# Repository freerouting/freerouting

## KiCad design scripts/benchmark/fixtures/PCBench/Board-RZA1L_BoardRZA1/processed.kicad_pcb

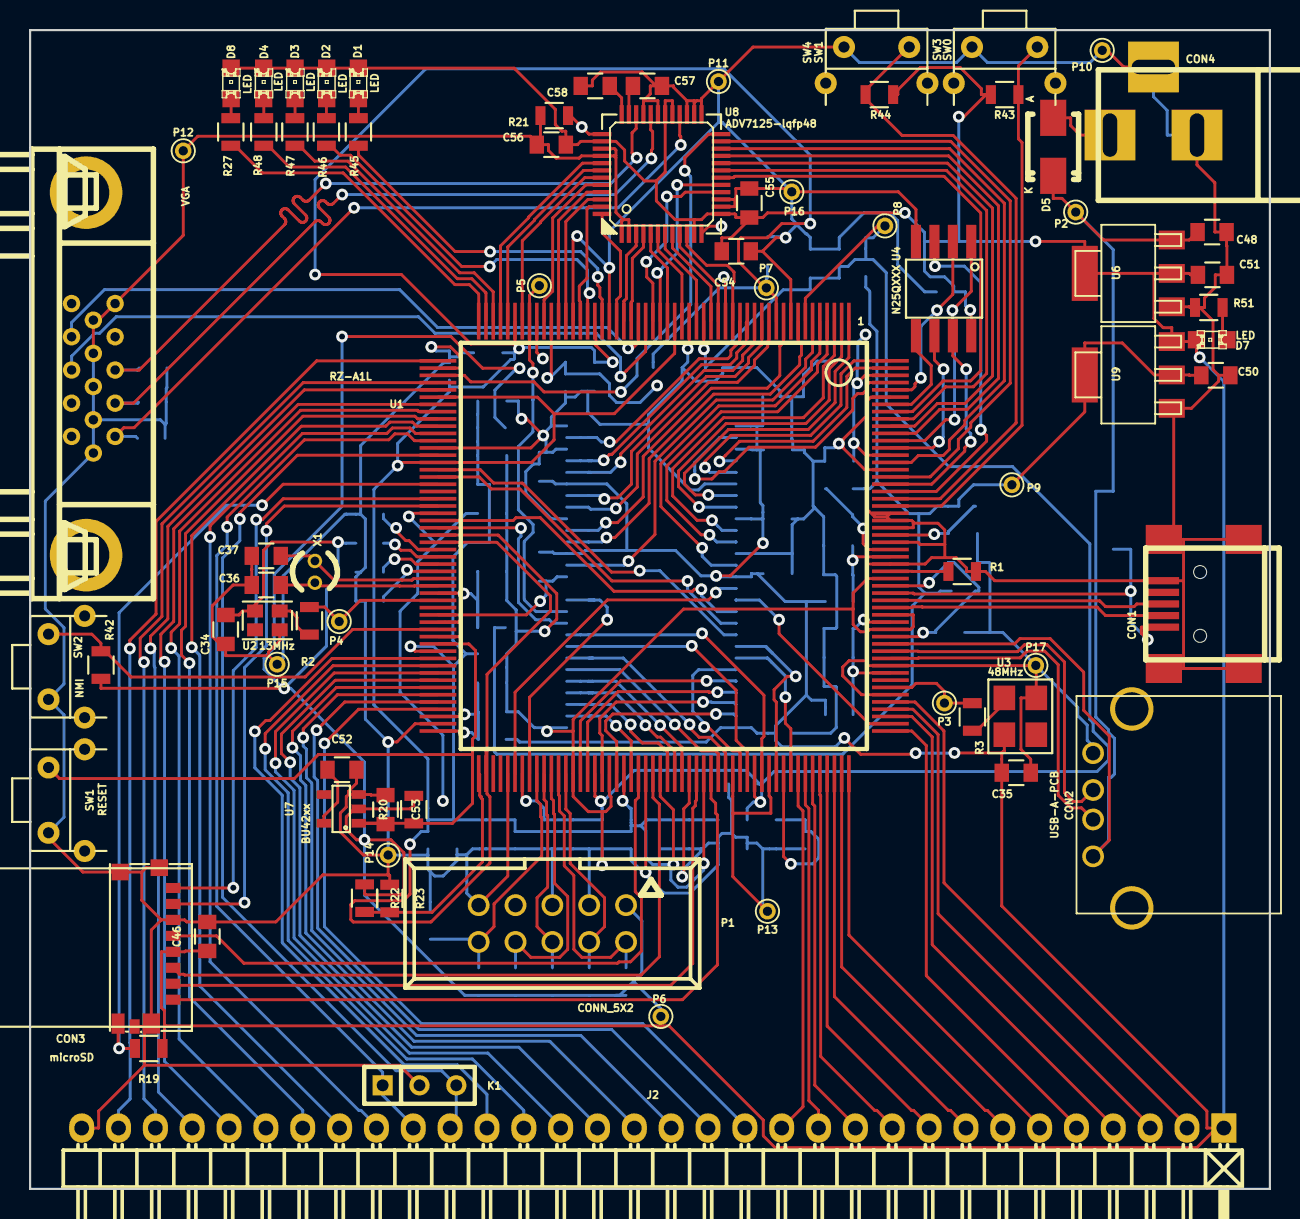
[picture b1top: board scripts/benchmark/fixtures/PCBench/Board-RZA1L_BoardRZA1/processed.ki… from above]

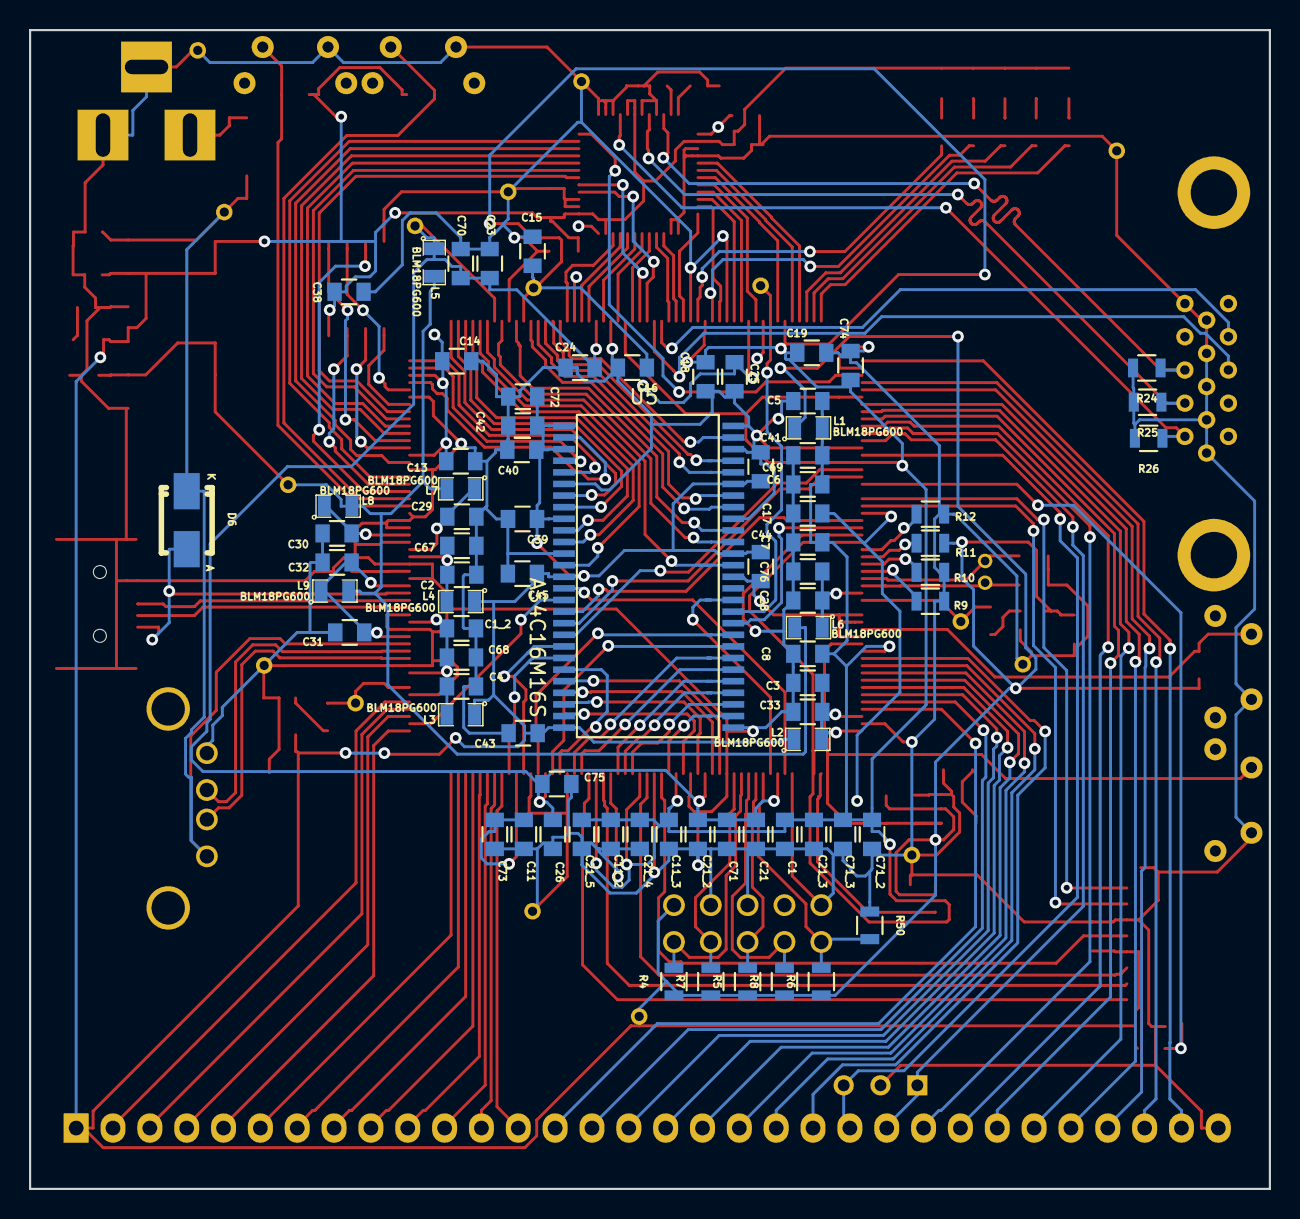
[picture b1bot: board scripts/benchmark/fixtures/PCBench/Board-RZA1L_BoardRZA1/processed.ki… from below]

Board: 4 copper layers, 85.5 x 79.9 mm, 154 parts (78 on the bottom side), 167 nets.

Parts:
C1, C1_2, C2, C3, C4, C5, C6, C7, C8, C11, C11_2, C11_3, C13, C14, C15, C16, C17, C18, C19, C21, C21_2, C21_3, C21_4, C21_5, C23, C24, C25, C26, C28, C29, C30, C31, C32, C33, C34, C35, C38, C39, C40, C41, C42, C43, C44, C45, C51, C52, C54, C55, C56, C57, C58: 100n; C_0805
C36, C37: 10p; C_0805
C46, C50, C53: 1u; C_0805
C48, C67, C68, C69, C70, C71_3: 10u; C_0805
C71, C71_2, C72, C73, C74, C75, C76: 100p; C_0805
CON1: USB-MINI-B; USB_MINI_B
CON2: USB-A-PCB; USB_A
CON3: microSD
CON4: BARREL_JACK
D1, D2, D3, D4, D7, D8: LED; LED-0805
D5, D6: MBRA210; Diode-SMA_Standard
J1: VGA; DB_15F-VGA
J2: SUPP32; Pin_Header_Angled_1x32
K1: CONN_3; SIL-3
L1, L2, L3, L4, L5, L6, L7, L8, L9: BLM18PG600; SM0805
P1: CONN_5X2; VASCH5x2
P2, P3, P4, P5, P6, P7, P8, P9, P10, P11, P12, P13, P14, P15, P16, P17: CONN_1; PINTST
R1: 5K6; R_0805
R2, R3, R51: 220R; R_0805
R4, R5, R6, R7, R8, R9, R10, R11, R12, R19, R20, R22, R23, R42, R43, R44, R50: 10k; R_0805
R21: 560R; R_0805
R24, R25, R26: 75R; R_0805
R27, R45, R46, R47, R48: 1k; R_0805
SW1: RESET; RigthAnglePush
SW2: NMI; RigthAnglePush
SW3: SW0; RigthAnglePush
SW4: SW1; RigthAnglePush
U1: RZ-A1L; PQFP208
U2: 13MHz; OSC_2x2p5
U3: 48MHz; OSC_4PIN
U4: N25QXXX; SOP2-8
U5: AS4C16M16S; TSOP_II_54
U6: NCP1117ST33T3G; sot223
U7: BU42xx; SSOP-5
U8: ADV7125-lqfp48; lqfp48
U9: NCP1117ST12T3G; sot223
X1: 32.768k; Crystal_Round_Vertical_3mm

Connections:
+1.2V: C50.1, L5.2, L6.2, L7.2, L8.2, L9.2, P9.1, U9.2
+3.3V: C34.1, C35.1, C38.1, C39.1, C40.1, C41.1, C42.1, C43.1, C44.1, C45.1, C46.1, C51.1, C54.2, C55.2, C56.2, C72.1, CON3.4, D1.2, D2.2, D3.2, D4.2, D7.2, D8.2, J2.1, L1.1, L2.1, L3.1, L4.1, P1.1, P6.1, R4.1, R5.1, R6.1, R7.1, R8.1, R11.1, R19.1, R20.2, R22.1, R42.2, R43.2, R44.2, U2.4, U3.4, U4.8, U5.1, U5.3, U5.9, U5.14, U5.27, U5.43, U5.49, U6.2, U7.2, U8.11, U8.13, U8.29, U8.30, U8.38, U9.3
/+5v: C48.1, CON2.1, D5.2, D6.2, P2.1, U1.169, U6.3
/AVcc: C3.1, C33.2, L2.2, U1.102, U1.104
/DCIN: CON4.1, D5.1
/DM_CLK: R10.2, U1.81
/D_D+: CON1.3, U1.175
/D_D-: CON1.2, U1.174
/H_D+: CON2.3, U1.168
/H_D-: CON2.2, U1.167
/JTAG_TCK: P1.4, R7.2, U1.117
/JTAG_TDI: P1.8, R8.2, U1.115
/JTAG_TDO: P1.6, R5.2, U1.114
/JTAG_TMS: P1.2, R4.2, U1.116
/JTAG_TRST: P1.10, R6.2, R50.2, U1.113
/LCD_DATA0: U1.192, U8.23
/LCD_DATA1: U1.194, U8.22
/LCD_DATA2: U1.198, U8.21
/LCD_DATA3: U1.199, U8.20
/LCD_DATA4: U1.200, U8.19
/LCD_DATA5: U1.201, U8.18
/LCD_DATA6: U1.27, U8.17
/LCD_DATA7: U1.28, U8.16
/LCD_DATA8: U1.17, U8.10
/LCD_DATA9: U1.19, U8.9
/LCD_DATA10: U1.20, U8.8
/LCD_DATA11: U1.22, U8.7
/LCD_DATA12: U1.24, U8.6
/LCD_DATA13: U1.26, U8.5
/LCD_DATA14: U1.31, U8.4
/LCD_DATA15: U1.32, U8.3
/LCD_DATA16: U1.33, U8.48
/LCD_DATA17: U1.38, U8.47
/LCD_DATA18: U1.40, U8.46
/LCD_DATA19: U1.41, U8.45
/LCD_DATA20: U1.43, U8.44
/LCD_DATA21: U1.46, U8.43
/LCD_DATA22: U1.48, U8.42
/LCD_DATA23: U1.49, U8.41
/LCD_HSYNC: J1.13, U1.29
/LCD_PCLK: U1.55, U8.24
/LCD_VSYNC: J1.14, U1.30
/LED0: R45.1, U1.35
/LED1: R46.1, U1.37
/LED2: R47.1, U1.50
/LED3: R48.1, U1.51
/LED4: R27.1, U1.52
/MD_BOOT0: R12.2, U1.79
/MD_BOOT1: R11.2, U1.80
/MD_CLKS: R9.2, U1.82
/NMI: R42.1, SW2.1, U1.90
/P1_0: J2.13, U1.149
/P1_1: J2.12, U1.150
/P1_2: J2.11, U1.151
/P1_3: J2.10, U1.152
/P1_4: J2.9, U1.153
/P1_5: J2.8, U1.154
/P1_6: J2.7, U1.155
/P1_7: J2.6, U1.156
/P1_8: J2.21, U1.94
/P1_9: J2.20, U1.95
/P1_10: J2.19, U1.96
/P1_11: J2.18, U1.97
/P1_12: J2.17, U1.98
/P1_13: J2.16, U1.99
/P1_14: J2.15, U1.100
/P1_15: J2.14, U1.101
/P2_7: J2.4, U1.159
/P2_8: J2.3, U1.160
/P2_9: J2.2, U1.161
/P3_15: J2.5, U1.157
/P7_3: J2.31, U1.53
/P7_5: J2.30, U1.56
/P7_6: J2.29, U1.57
/P7_7: J2.28, U1.59
/P7_8: J2.27, U1.60
/P7_9: J2.26, U1.61
/P7_10: J2.25, U1.62
/P7_11: J2.24, U1.63
/P8_12(RXD): J2.23, K1.1, U1.64
/P8_13(TXD): J2.22, K1.3, U1.66
/PLLVCC: C28.1, C76.1, L6.1, U1.85
/PVCC: C1.1, C5.1, C6.1, C7.1, C8.1, C11.1, C11_2.1, C11_3.1, C13.1, C14.1, C15.1, C16.1, C18.1, C19.1, C21_3.1, C21_4.1, C21_5.1, C69.1, C71_2.1, C71_3.1, C73.1, C74.1, L1.2, P7.1, U1.11, U1.25, U1.36, U1.47, U1.58, U1.67, U1.78, U1.93, U1.106, U1.125, U1.130, U1.136, U1.147, U1.195, U1.206
/RAM_A1: U1.119, U5.23
/RAM_A2: U1.120, U5.24
/RAM_A3: U1.122, U5.25
/RAM_A4: U1.124, U5.26
/RAM_A5: U1.126, U5.29
/RAM_A6: U1.131, U5.30
/RAM_A7: U1.132, U5.31
/RAM_A8: U1.133, U5.32
/RAM_A9: U1.138, U5.33
/RAM_A10: U1.139, U5.34
/RAM_A11: U1.141, U5.22
/RAM_A12: U1.142, U5.35
/RAM_A13: U1.144, U5.36
/RAM_A14: U1.146, U5.20
/RAM_A15: U1.148, U5.21
/RAM_CAS: U1.75, U5.17
/RAM_CKE: U1.76, U5.37
/RAM_CLK: P5.1, U1.45, U5.38
/RAM_CS: U1.68, U5.19
/RAM_D0: U1.205, U5.2
/RAM_D1: U1.207, U5.4
/RAM_D2: U1.208, U5.5
/RAM_D3: U1.1, U5.7
/RAM_D4: U1.2, U5.8
/RAM_D5: U1.3, U5.10
/RAM_D6: U1.4, U5.11
/RAM_D7: U1.5, U5.13
/RAM_D8: U1.6, U5.42
/RAM_D9: U1.8, U5.44
/RAM_D10: U1.10, U5.45
/RAM_D11: U1.12, U5.47
/RAM_D12: U1.13, U5.48
/RAM_D13: U1.14, U5.50
/RAM_D14: U1.15, U5.51
/RAM_D15: U1.16, U5.53
/RAM_DQMH: U1.112, U5.39
/RAM_DQML: U1.110, U5.15
/RAM_RAS: U1.69, U5.18
/RAM_RDnWR: U1.158, U5.16
/RESET: C53.2, R20.1, SW1.1, U1.92, U7.1
/SD_CD_1: CON3.G5, R19.2, U1.70
/SD_CLK_1: CON3.5, U1.127
/SD_CMD_1: CON3.3, U1.129
/SD_D0_1: CON3.7, U1.73
/SD_D1_1: CON3.8, U1.72
/SD_D2_1: CON3.1, U1.137
/SD_D3_1: CON3.2, U1.135
/SPBCLK_0: U1.196, U4.6
/SPBIO_00_0: U1.202, U4.5
/SPBIO_10_0: U1.204, U4.2
/SPBIO_20_0: U1.190, U4.3
/SPBIO_30_0: U1.191, U4.7
/SPBSSL_0: U1.197, U4.1
/SW0: R43.1, SW3.1, U1.188
/SW1: R44.1, SW4.1, U1.189
/SYS_CLK: P4.1, R2.1, U1.86
/USBAPVCC: C2.1, C67.1, L4.2, U1.181
/USBAVCC: C29.1, L7.1, U1.182
/USBDPVCC: C1_2.1, C4.1, C68.1, L3.2, U1.165, U1.172
/USBDVCC: C31.1, C32.1, L9.1, U1.170, U1.177
/USBUVCC: C30.1, L8.1, U1.184
/USB_CLK: P3.1, R3.1, U1.163
/VBUS: CON1.1, D6.1, U1.176
/VCC: C17.1, C21.1, C21_2.1, C23.1, C24.1, C25.1, C26.1, C70.1, C71.1, C75.1, L5.1, P8.1, U1.7, U1.21, U1.42, U1.74, U1.111, U1.121, U1.143
/VGAB: J1.1, R26.1, U8.28
/VGAG: J1.2, R25.1, U8.32
/VGAR: J1.3, R24.1, U8.34
unnamed: C36.2, U1.84, X1.1
unnamed: C37.2, U1.83, X1.2
unnamed: C52.1, U7.5
unnamed: C57.1, U8.35
unnamed: C58.1, U8.36
unnamed: D1.1, R45.2
unnamed: D2.1, R46.2
unnamed: D3.1, R47.2
unnamed: D4.1, R48.2
unnamed: D7.1, R51.2
unnamed: D8.1, R27.2
unnamed: R1.2, U1.179
unnamed: R2.2, U2.3
unnamed: R3.2, U3.3
unnamed: R21.1, U8.37
unnamed: R22.2, R23.2, U1.105
VSS: C1.2, C1_2.2, C2.2, C3.2, C4.2, C5.2, C6.2, C7.2, C8.2, C11.2, C11_2.2, C11_3.2, C13.2, C14.2, C15.2, C16.2, C17.2, C18.2, C19.2, C21.2, C21_2.2, C21_3.2, C21_4.2, C21_5.2, C23.2, C24.2, C25.2, C26.2, C28.2, C29.2, C30.2, C31.2, C32.2, C33.1, C34.2, C35.2, C36.1, C37.1, C38.2, C39.2, C40.2, C41.2, C42.2, C43.2, C44.2, C45.2, C46.2, C48.2, C50.2, C51.2, C52.2, C53.1, C54.1, C55.1, C56.1, C57.2, C58.2, C67.2, C68.2, C69.2, C70.2, C71.2, C71_2.2, C71_3.2, C72.2, C73.2, C74.2, C75.2, C76.2, CON1.5, CON1.6, CON1.7, CON1.8, CON1.9, CON2.4, CON3.6, CON3.G1, CON3.G2, CON3.G3, CON3.G4, CON4.2, CON4.3, J1.5, J1.6, J1.7, J1.8, J1.9, J1.10, J2.32, K1.2, P1.3, P1.5, P1.9, P10.1, P11.1, P12.1, P13.1, P14.1, P15.1, P16.1, P17.1, R1.1, R9.1, R10.1, R12.1, R21.2, R23.1, R24.2, R25.2, R26.2, R50.1, R51.1, SW1.2, SW2.2, SW3.2, SW4.2, U1.9, U1.18, U1.23, U1.34, U1.39, U1.44, U1.54, U1.65, U1.77, U1.88, U1.89, U1.91, U1.103, U1.109, U1.118, U1.123, U1.128, U1.134, U1.140, U1.145, U1.162, U1.166, U1.171, U1.173, U1.178, U1.180, U1.183, U1.185, U1.186, U1.187, U1.193, U1.203, U2.2, U3.2, U4.4, U5.6, U5.12, U5.28, U5.41, U5.46, U5.52, U5.54, U6.1, U7.3, U8.1, U8.2, U8.12, U8.14, U8.15, U8.25, U8.26, U8.27, U8.31, U8.33, U8.39, U8.40, U9.1

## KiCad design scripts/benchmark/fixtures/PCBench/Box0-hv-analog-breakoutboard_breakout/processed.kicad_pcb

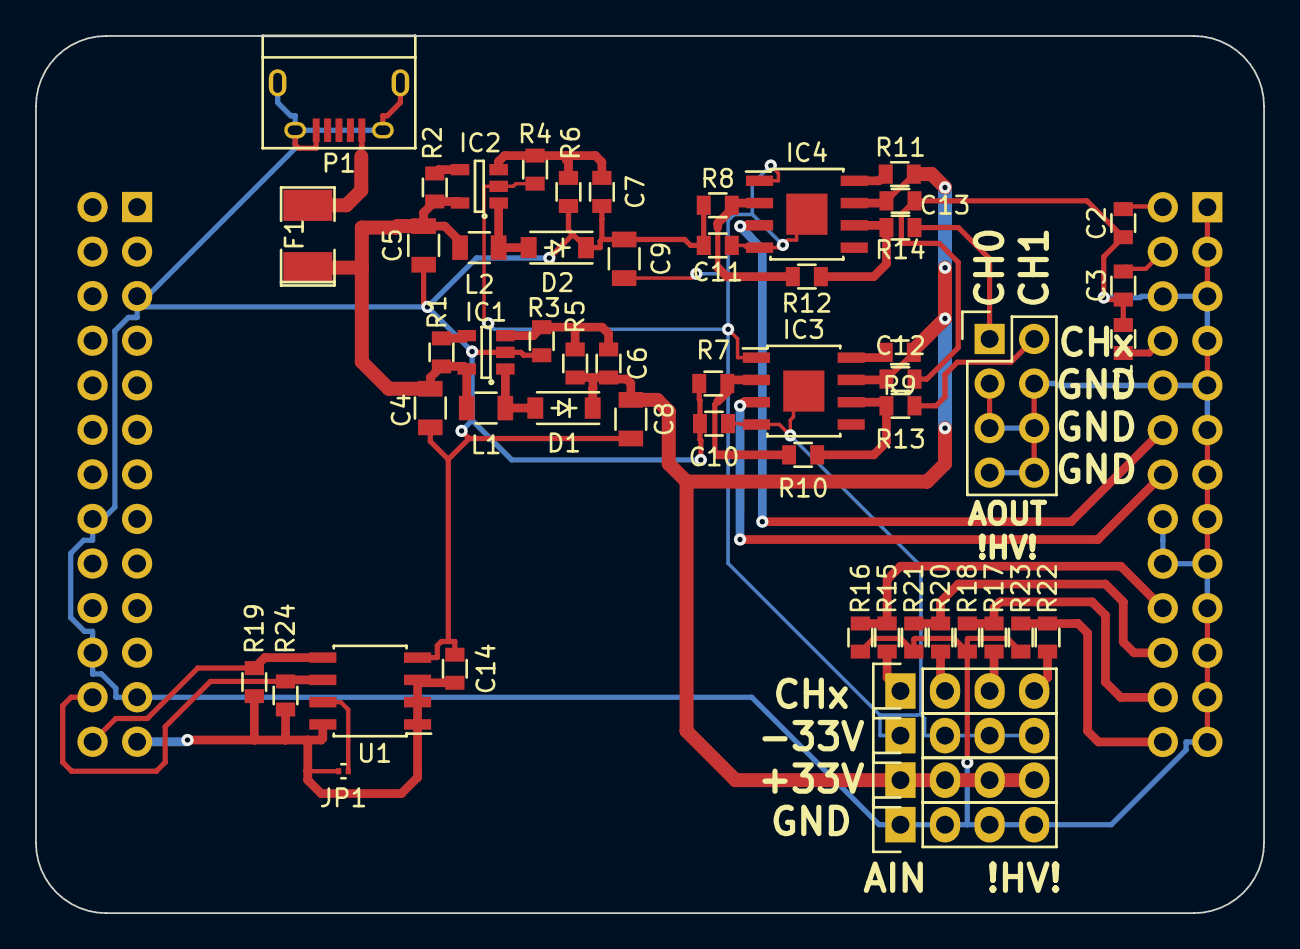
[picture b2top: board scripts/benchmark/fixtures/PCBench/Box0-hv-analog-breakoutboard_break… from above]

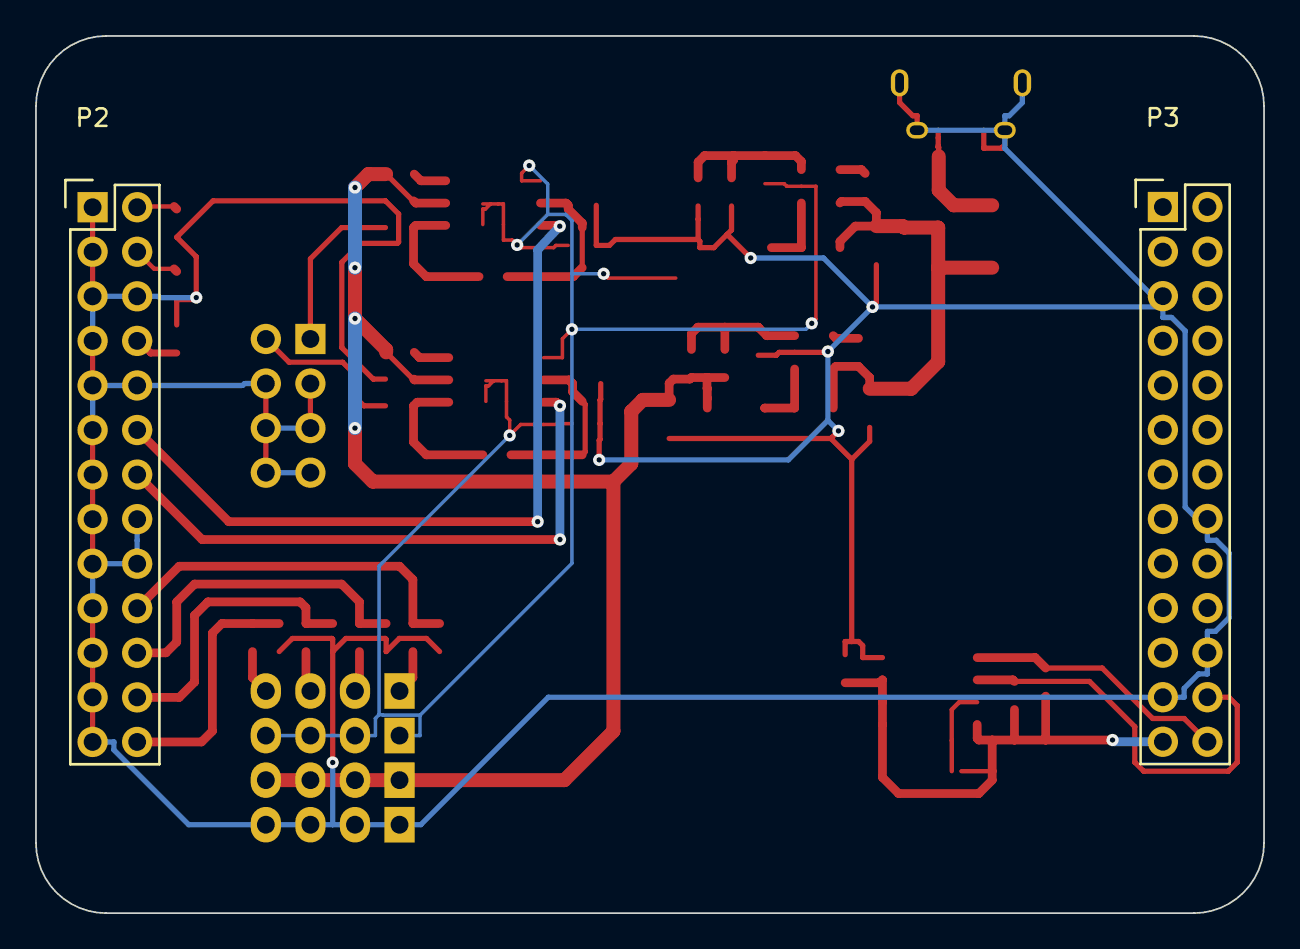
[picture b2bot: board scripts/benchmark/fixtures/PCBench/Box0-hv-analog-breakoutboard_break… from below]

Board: 2 copper layers, 70.0 x 50.0 mm, 57 parts (2 on the bottom side), 36 nets.

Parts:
C1, C2, C3: 100nF; 0603
C4, C5: 4.7u; 0805
C6, C7: 82p; 0603
C8, C9: 10u; 0805
C10, C11, C12, C13, C14: 100n; 0603
D1, D2: MBR0540; SOD-123
F1: F_Small; SMD-1210_Pol
IC1, IC2: LM2733; SOT-23-5
IC3, IC4: OPA454; SOIC-8-3.9*4.9mm_HP_to_P4
JP1: Jumper_NO_Small; C_0201
L1, L2: 10u; 0805
P1: USB_OTG; USB_Micro-B
P2: BASE_BOARD_ANALOG; Pin_Header_Straight_2x13
P3: BASE_BOARD_DIGITAL; Pin_Header_Straight_2x13
P4: CONN_02X04; Pin_Header_Straight_2x04
P5, P6, P7, P8: CONN_01X04; Pin_Header_Straight_1x04
R1, R2: 47K; 0603
R3, R4: 12K; 0603
R5, R6: 309K; 0603
R7, R8, R16, R18, R21, R23: 10K; 0603
R9, R11: 1M; 0603
R10, R12, R15, R17, R20, R22: 91K; 0603
R13, R14: 10R; 0603
R19, R24: 4.7K; 0603
U1: 24C16; SOIC-8_3.9x4.9mm_Pitch1.27mm

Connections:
5V: C4.1, C5.1, F1.1, IC1.5, IC2.5, L1.2, L2.2, R1.1, R2.1
+33V: C6.2, C8.1, C12.1, C13.1, D1.1, IC3.7, IC4.7, P6.1, P6.2, P6.3, P6.4, R5.2, R9.1, R11.1
-33V: C9.2, C10.1, C11.1, IC2.2, IC3.1, IC3.4, IC4.1, IC4.4, P7.1, P7.2, P7.3, P7.4, R4.2
/Box0 Interface/AIN0.0: P2.20, R15.1, R16.2
/Box0 Interface/AIN0.1: P2.22, R20.1, R21.2
/Box0 Interface/AIN0.2: P2.24, R17.1, R18.2
/Box0 Interface/AIN0.3: P2.26, R22.1, R23.2
/Box0 Interface/AOUT0.0: IC4.3, P2.12
/Box0 Interface/AOUT0.1: IC3.3, P2.14
/Box0 Interface/I2C0.SCL: P3.24, R24.2, U1.6
/Box0 Interface/I2C0.SDA: P3.26, R19.2, U1.5
ANALOG_NEG: C3.1, P2.4
ANALOG_POS: C2.1, P2.2
DIGITAL_EXT: C14.1, JP1.1, P3.25, R19.1, R24.1, U1.1, U1.2, U1.3, U1.8
GND: C1.2, C2.2, C3.2, C4.2, C5.2, C7.2, C8.2, C9.1, C10.2, C11.2, C12.2, C13.2, C14.2, D2.1, IC1.2, P1.5, P1.6, P2.1, P2.3, P2.5, P2.6, P2.7, P2.9, P2.10, P2.11, P2.13, P2.15, P2.16, P2.17, P2.18, P2.19, P2.21, P2.23, P2.25, P3.5, P3.16, P3.22, P3.23, P4.3, P4.4, P4.5, P4.6, P4.7, P4.8, P5.1, P5.2, P5.3, P5.4, R3.2, R6.2, R7.1, R8.1, R16.1, R18.1, R21.1, R23.1, U1.4
unnamed: C6.1, IC1.3, R3.1, R5.1
unnamed: C7.1, IC2.3, R4.1, R6.1
unnamed: D1.2, IC1.1, L1.1
unnamed: D2.2, IC2.1, L2.1
unnamed: F1.2, P1.1
unnamed: IC1.4, R1.2
unnamed: IC2.4, R2.2
unnamed: IC3.2, R7.2, R10.2
unnamed: IC3.6, R10.1, R13.2
unnamed: IC3.8, R9.2
unnamed: IC4.2, R8.2, R12.2
unnamed: IC4.6, R12.1, R14.2
unnamed: IC4.8, R11.2
unnamed: JP1.2, U1.7
unnamed: P4.1, R14.1
unnamed: P4.2, R13.1
unnamed: P8.1, R15.2
unnamed: P8.2, R20.2
unnamed: P8.3, R17.2
unnamed: P8.4, R22.2
VREF_EXT: C1.1, P2.8

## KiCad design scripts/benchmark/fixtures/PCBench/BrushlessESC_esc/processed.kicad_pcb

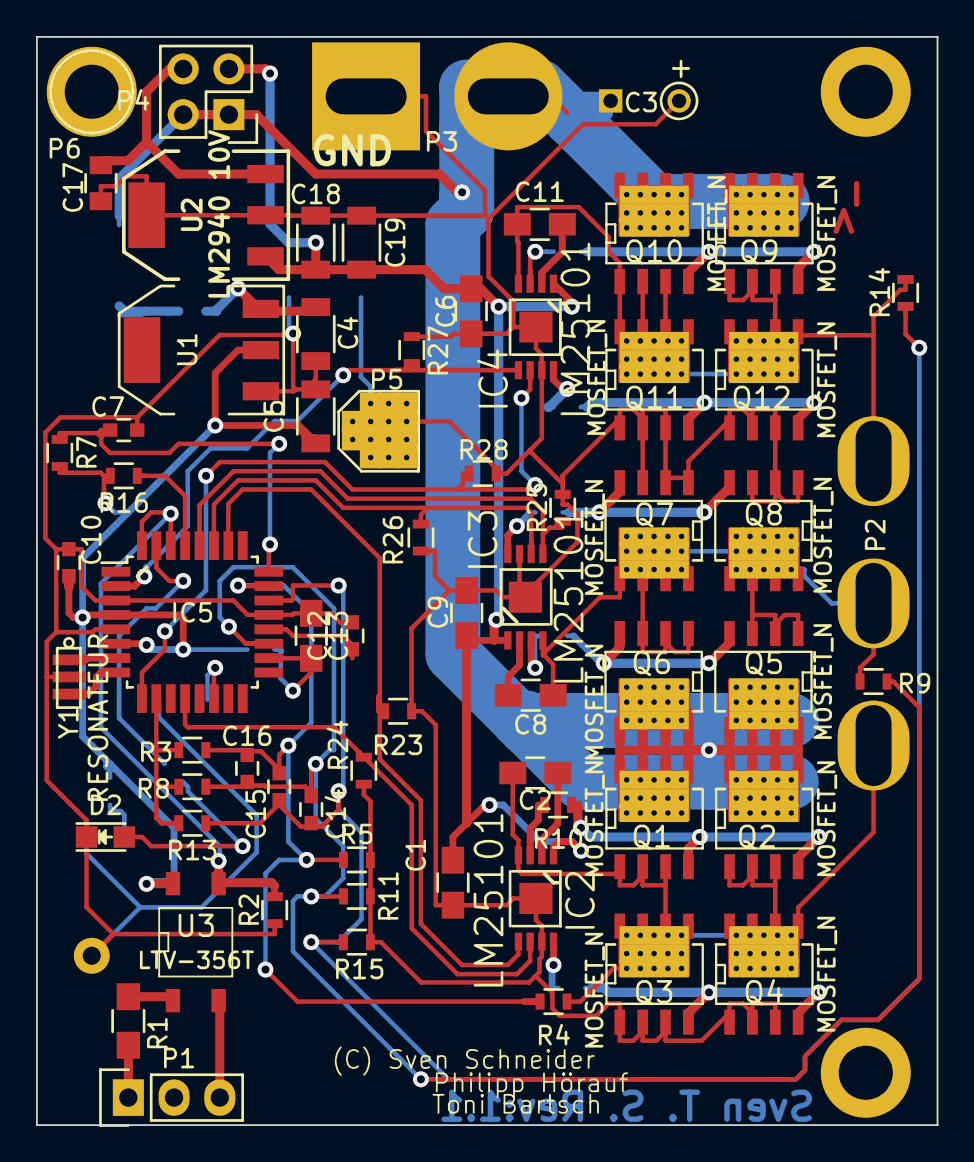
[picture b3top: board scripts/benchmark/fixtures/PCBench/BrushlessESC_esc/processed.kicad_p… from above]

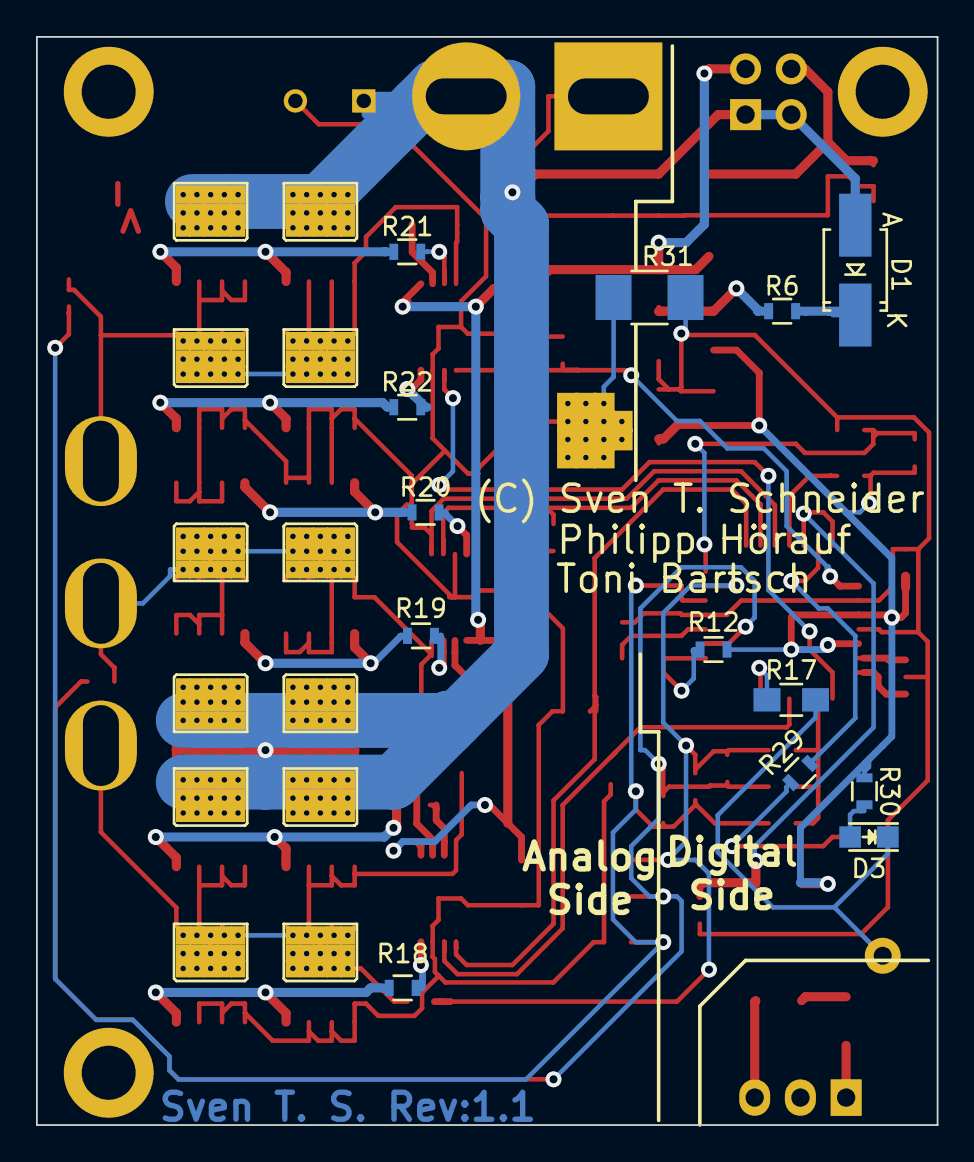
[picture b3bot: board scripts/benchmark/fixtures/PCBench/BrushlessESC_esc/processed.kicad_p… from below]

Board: 2 copper layers, 50.0 x 60.5 mm, 79 parts (13 on the bottom side), 50 nets.

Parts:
C1, C2, C6, C8, C9, C11, C13: 1µ; C_0805_HandSoldering
C3: 220µ; C_Radial_D8_L13_P3.8
C4, C5, C18, C19: 10µ; C_1206
C7, C10, C12, C14, C15, C16: 100n; C_0603
C17: 470n; C_0805
D1: DIODE; SMA_Handsoldering
D2, D3: LED; LED-0805
IC2, IC3, IC4: LM25101; 8-MSOP
IC5: ATMEGA8-AI; TQFP-32_7x7mm_Pitch0.8mm
P1, P2: CONN_01X03; Socket_Strip_Straight_1x03
P3: CONN_01X02; Socket_Strip_Straight_1x02
P4: CONN_02X02; Socket_Strip_Straight_2x02
P5, P6: CONN_01X01; 1pin
Q1, Q2, Q3, Q4, Q5, Q6, Q7, Q8, Q9, Q10, Q11, Q12: MOSFET_N; SO8_WITH_Heatpipes_New
R1: R; R_0805_HandSoldering
R2: 10k; R_0603
R3, R5, R8, R11, R13, R15, R16: 3k3; R_0603
R4, R9, R14: 18k; R_0603
R6: 1; R_0603
R7: 1k5; R_0603
R10, R18, R19, R20, R21, R22: R; R_0603
R12, R29, R30: 100; R_0603
R17: 0 Bridge; R_0805_HandSoldering
R23, R24, R25, R26, R27, R28: PD; R_0603
R31: Bridge; R_1210_HandSoldering
U1: LD1117S50TR; SOT-223
U2: LM2940 10V; SOT223_GND_VO_VI
U3: LTV-356T; SO-4
Y1: RESONATEUR; CerOsc_3,2x1,3

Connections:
9V: C1.1, C6.1, C9.1, C18.1, C19.1, IC2.1, IC3.1, IC4.1, P4.2, U2.1
+5V: C5.1, C10.1, IC5.4, IC5.6, R7.2, R12.2, R16.2, R30.2, U1.2, U3.4
/A_Highside_Gate: Q1.G, Q2.G, R10.1
/A_Lowside_Gate: Q3.G, Q4.G, R18.1
/B_Highside_Gate: Q5.G, Q6.G, R19.1
/B_Lowside_Gate: Q7.G, Q8.G, R20.1
/C_Highside_Gate: Q9.G, Q10.G, R21.1
/C_Lowside_Gate: Q11.G, Q12.G, R22.1
/INPUT_GND: P1.3, U3.2
/INPUT_SIGNAL: P1.1, R1.2
/VBat_to_10V: C17.1, P4.4, U2.3
A: C2.2, IC2.4, P2.1, Q1.S, Q2.S, Q3.D, Q4.D, R4.1
A+: IC2.5, IC5.26, R23.2
A-: IC2.6, IC5.12, R24.2
B: C8.2, IC3.4, P2.2, Q5.S, Q6.S, Q7.D, Q8.D, R9.1
B+: IC3.5, IC5.28, R25.2
B-: IC3.6, IC5.27, R26.2
C: C11.2, IC4.4, P2.3, Q9.S, Q10.S, Q11.D, Q12.D, R14.1
C+: IC4.5, IC5.2, R27.2
C-: IC4.6, IC5.9, R28.2
D_GND: C4.2, C5.2, C7.2, C10.2, C12.2, C13.1, D2.1, D3.1, IC5.3, IC5.5, IC5.21, P6.1, R2.1, R17.2, R31.2, U1.1, Y1.2
GND: C1.2, C3.2, C6.2, C9.2, C17.2, C18.2, C19.2, IC2.7, IC2.PAD, IC3.7, IC3.PAD, IC4.7, IC4.PAD, P3.1, P5.1, Q3.S, Q4.S, Q7.S, Q8.S, Q11.S, Q12.S, R5.2, R11.2, R15.2, R23.1, R24.1, R25.1, R26.1, R27.1, R28.1, R31.1, U2.2
M: IC5.10, R3.2, R8.2, R13.2
unnamed: C2.1, IC2.2
unnamed: C4.1, R6.1, U1.3
unnamed: C8.1, IC3.2
unnamed: C11.1, IC4.2
unnamed: C12.1, IC5.20
unnamed: C13.2, IC5.18, R12.1
unnamed: D1.2, R6.2
unnamed: D2.2, R29.1
unnamed: D3.2, R30.1
unnamed: IC2.3, R10.2
unnamed: IC2.8, R18.2
unnamed: IC3.3, R19.2
unnamed: IC3.8, R20.2
unnamed: IC4.3, R21.2
unnamed: IC4.8, R22.2
unnamed: IC5.7, Y1.1
unnamed: IC5.8, Y1.3
unnamed: IC5.14, R17.1
unnamed: IC5.29, R16.1
unnamed: IC5.31, R29.2
unnamed: R1.1, U3.1
PWM: IC5.30, IC5.32, R2.2, U3.3
S_A: C15.1, C16.1, IC5.23, R3.1, R4.2, R5.1
S_B: C14.2, C16.2, IC5.19, R8.1, R9.2, R11.1
S_C: C14.1, C15.2, IC5.22, R13.1, R14.2, R15.1
S_PWR: C7.1, IC5.24, R7.1
V_BAT: C3.1, D1.1, P3.2, P4.1, P4.3, Q1.D, Q2.D, Q5.D, Q6.D, Q9.D, Q10.D
